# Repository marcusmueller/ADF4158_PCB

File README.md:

# ADF4158 + HMC391 PCB

This project is a PCB that contains an
[ADF4158](https://www.analog.com/en/products/adf4158.html) direct
modulation/waveform generating fractional-N frequency synthesizer and a
[HMC391](https://www.analog.com/en/products/hmc391.html) 3.9 - 4.45 GHz VCO. The
board is primarily intended as an LO source for a 10 GHz FMCW radar inspired by
the
[ADALM-PHASER](https://wiki.analog.com/resources/eval/user-guides/circuits-from-the-lab/cn0566/overview_setup). The
VCO output can be used with a subharmonic mixer and an IF around 1.6 GHz to
cover the 10 - 10.5 GHz amateur radio band.

The board runs from a 12 - 16 VDC supply, exposes all the control pins of the
ADF4158 in a 2.58 mm pin header (3.3V logic) and includes an optional 10 MHz
reference input. The BOM cost is around 45€.

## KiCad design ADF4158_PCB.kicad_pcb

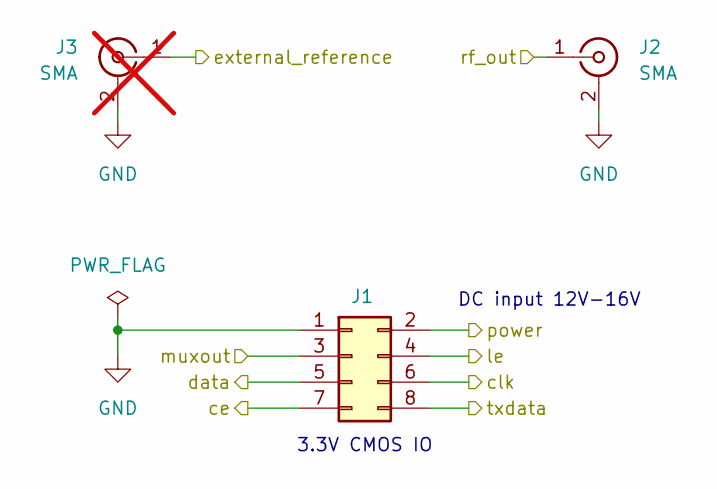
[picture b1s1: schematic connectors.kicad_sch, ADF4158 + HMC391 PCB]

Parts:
J1: Conn_02x04_Odd_Even; PinHeader_2x04_P2.54mm_Vertical; Digikey Part Number 2057-PH2-08-UA-ND
J2: SMA; WRL-23187; Digikey Part Number 1568-WRL-23187-ND
J3: SMA; WRL-23187; Digikey Part Number 1568-WRL-23187-ND; not fitted

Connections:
/ADF4158 + HMC391/ce: J1.7; also elsewhere on the board
/ADF4158 + HMC391/clk: J1.6; also elsewhere on the board
/ADF4158 + HMC391/data: J1.5; also elsewhere on the board
/ADF4158 + HMC391/external_reference: J3.1 (In); also elsewhere on the board
/ADF4158 + HMC391/le: J1.4; also elsewhere on the board
/ADF4158 + HMC391/txdata: J1.8; also elsewhere on the board
/Connectors/power: J1.2; also elsewhere on the board
/muxout: J1.3; also elsewhere on the board
/rf_out: J2.1 (In); also elsewhere on the board
GND: J1.1, J2.2 (Ext), J3.2 (Ext); also elsewhere on the board

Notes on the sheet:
DC input 12V-16V
3.3V CMOS IO

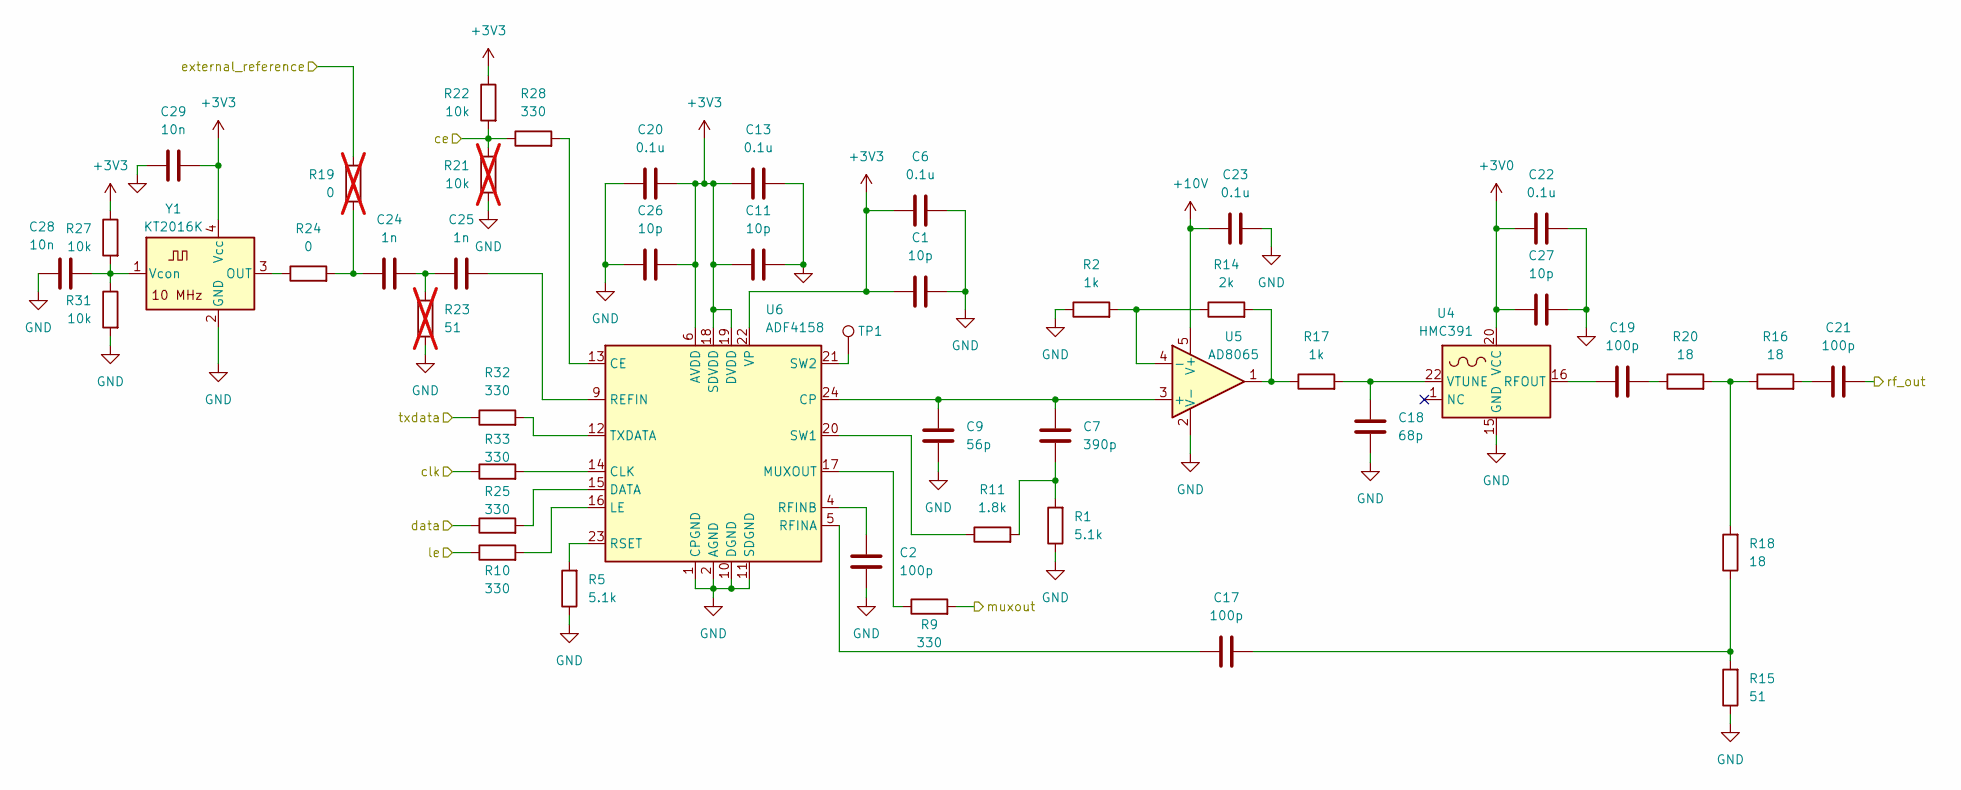
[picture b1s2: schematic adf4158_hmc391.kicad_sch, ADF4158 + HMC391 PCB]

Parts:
C1, C11, C26, C27: 10p; C_0402_1005Metric; Digikey Part Number 1276-1139-1-ND
C2, C17, C19, C21: 100p; C_0402_1005Metric; Digikey Part Number 1276-1025-1-ND
C6, C13, C20, C22, C23: 0.1u; C_0402_1005Metric; Digikey Part Number 1276-1002-1-ND
C7: 390p; C_0402_1005Metric; Digikey Part Number 490-1296-1-ND
C9: 56p; C_0402_1005Metric; Digikey Part Number 490-1288-1-ND
C18: 68p; C_0402_1005Metric; Digikey Part Number 490-5876-1-ND
C24, C25: 1n; C_0402_1005Metric; Digikey Part Number 1276-1032-1-ND
C28, C29: 10n; C_0402_1005Metric; Digikey Part Number 1276-1028-1-ND
R1, R5: 5.1k; R_0402_1005Metric; Digikey Part Number P5.1KDCCT-ND
R2, R17: 1k; R_0402_1005Metric; Digikey Part Number P1.00KLCT-ND
R9, R10, R25, R28, R32, R33: 330; R_0402_1005Metric; Digikey Part Number P330LCT-ND
R11: 1.8k; R_0402_1005Metric; Digikey Part Number P1.80KLCT-ND
R14: 2k; R_0402_1005Metric; Digikey Part Number P2.00KLCT-ND
R15: 51; R_0402_1005Metric; Digikey Part Number P51.0LCT-ND
R16, R18, R20: 18; R_0402_1005Metric; Digikey Part Number P18.0LCT-ND
R19: 0; R_0402_1005Metric; Digikey Part Number P0.0JCT-ND; not fitted
R21: 10k; R_0402_1005Metric; Digikey Part Number P10.0KLCT-ND; not fitted
R22, R27, R31: 10k; R_0402_1005Metric; Digikey Part Number P10.0KLCT-ND
R23: 51; R_0402_1005Metric; Digikey Part Number P51.0LCT-ND; not fitted
R24: 0; R_0402_1005Metric; Digikey Part Number P0.0JCT-ND
TP1: TestPoint; TestPoint_Pad_D2.0mm
U4: HMC391; QFN-24-1EP_4x4mm_P0.5mm_EP2.8x2.8mm; Digikey Part Number 505-HMC391LP4ECT-ND
U5: AD8065; TSOT-23-5; Digikey Part Number AD8065ARTZ-REELCT-ND
U6: ADF4158; LFCSP-24-1EP_4x4mm_P0.5mm_EP2.5x2.5mm; Digikey Part Number 505-ADF4158CCPZ-ND
Y1: KT2016K; Digikey Part Number 478-KT2016K10000ZAW33ZGKCT-ND

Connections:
+3V0: C22.2, C27.2, U4.20 (VCC); also elsewhere on the board
+3V3: C1.2, C6.2, C11.2, C13.2, C20.2, C26.2, C29.1, R22.1, R27.1, U6.6 (AVDD), U6.7 (AVDD), U6.8 (AVDD), U6.18 (SDVDD), U6.19 (DVDD), U6.22 (VP), Y1.4 (Vcc); also elsewhere on the board
+10V: C23.2, U5.5 (V+); also elsewhere on the board
/ADF4158 + HMC391/ce: R21.1, R22.2, R28.1; also elsewhere on the board
/ADF4158 + HMC391/clk: R33.1; also elsewhere on the board
/ADF4158 + HMC391/data: R25.1; also elsewhere on the board
/ADF4158 + HMC391/external_reference: R19.2; also elsewhere on the board
/ADF4158 + HMC391/le: R10.1; also elsewhere on the board
/ADF4158 + HMC391/txdata: R32.1; also elsewhere on the board
/muxout: R9.2; also elsewhere on the board
/rf_out: C21.2; also elsewhere on the board
GND: C1.1, C2.2, C6.1, C9.2, C11.1, C13.1, C18.2, C20.1, C22.1, C23.1, C26.1, C27.1, C28.1, C29.2, R1.1, R2.1, R5.1, R15.1, R21.2, R23.1, R31.2, U4.15 (GND), U4.25 (GND), U5.2 (V-), U6.1 (CPGND), U6.2 (AGND), U6.3 (AGND), U6.10 (DGND), U6.11 (SDGND), U6.25 (AGND), Y1.2 (GND); also elsewhere on the board
unnamed: C7.2, R1.2, R11.2
unnamed: C17.2, R15.2, R18.1
unnamed: C19.2, R20.1
unnamed: C21.1, R16.2
unnamed: C24.1, R19.1, R24.2
unnamed: C24.2, C25.1, R23.2
unnamed: R14.2, R17.1, U5.1
unnamed: R16.1, R18.2, R20.2
unnamed: C19.1, U4.16 (RFOUT)
unnamed: C18.1, R17.2, U4.22 (VTUNE)
unnamed: C7.1, C9.1, U5.3 (+), U6.24 (CP)
unnamed: R2.2, R14.1, U5.4 (-)
unnamed: R28.2, U6.13 (CE)
unnamed: R33.2, U6.14 (CLK)
unnamed: R25.2, U6.15 (DATA)
unnamed: R10.2, U6.16 (LE)
unnamed: R9.1, U6.17 (MUXOUT)
unnamed: C25.2, U6.9 (REFIN)
unnamed: C17.1, U6.5 (RFINA)
unnamed: C2.1, U6.4 (RFINB)
unnamed: R5.2, U6.23 (RSET)
unnamed: R11.1, U6.20 (SW1)
unnamed: TP1.1, U6.21 (SW2)
unnamed: R32.2, U6.12 (TXDATA)
unnamed: R24.1, Y1.3 (OUT)
unnamed: C28.2, R27.2, R31.1, Y1.1 (Vcon)

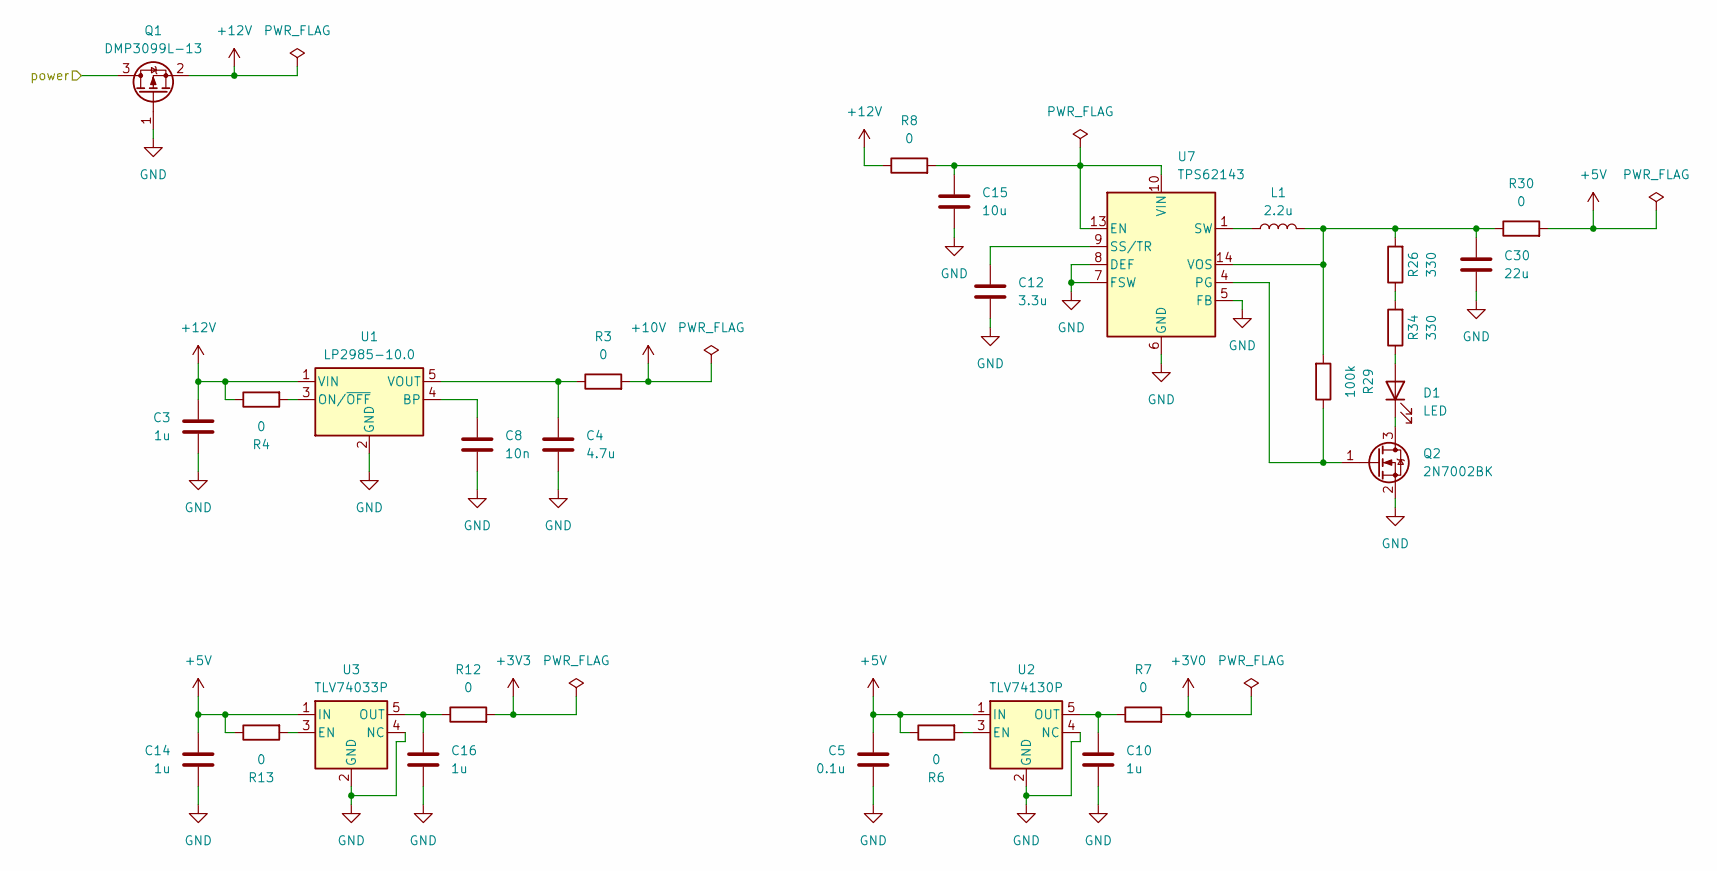
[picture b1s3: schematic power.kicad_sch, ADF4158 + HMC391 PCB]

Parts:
C3, C10, C14, C16: 1u; C_0603_1608Metric; Digikey Part Number 1276-1184-1-ND
C4: 4.7u; C_0805_2012Metric; Digikey Part Number 490-GRM21BR71C475ME51KCT-ND
C5: 0.1u; C_0402_1005Metric; Digikey Part Number 1276-1002-1-ND
C8: 10n; C_0402_1005Metric; Digikey Part Number 1276-1028-1-ND
C12: 3.3u; C_1206_3216Metric; Digikey Part Number 1276-1841-1-ND
C15: 10u; C_0805_2012Metric; Digikey Part Number 1276-2872-1-ND
C30: 22u; C_0603_1608Metric; Digikey Part Number 1276-1274-1-ND
D1: LED; LED_0603_1608Metric; Digikey Part Number 3147-B1931NG--20D001114U1930CT-ND
L1: 2.2u; L_1008_2520Metric; Digikey Part Number 490-10649-1-ND
Q1: DMP3099L-13; SOT-23-3; Digikey Part Number DMP3099L-13DICT-ND
Q2: 2N7002BK; SOT-23; Digikey Part Number 1727-4789-1-ND
R3, R4, R6, R7, R8, R12, R13, R30: 0; R_0402_1005Metric; Digikey Part Number P0.0JCT-ND
R26, R34: 330; R_0402_1005Metric; Digikey Part Number P330LCT-ND
R29: 100k; R_0402_1005Metric; Digikey Part Number P100KLCT-ND
U1: LP2985-10.0; SOT-23-5; Digikey Part Number 296-24263-1-ND
U2: TLV74130P; SOT-23-5; Digikey Part Number 296-50000-1-ND
U3: TLV74033P; SOT-23-5; Digikey Part Number 296-TLV74033PDBVRCT-ND
U7: TPS62143; VQFN-16-1EP_3x3mm_P0.5mm_EP1.68x1.68mm_ThermalVias; Digikey Part Number 296-39448-1-ND

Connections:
+3V0: R7.2; also elsewhere on the board
+3V3: R12.2; also elsewhere on the board
+5V: C5.1, C14.1, R6.1, R13.1, R30.2, U2.1 (IN), U3.1 (IN)
+10V: R3.2; also elsewhere on the board
+12V: C3.1, Q1.2 (S), R4.1, R8.1, U1.1 (VIN)
/Connectors/power: Q1.3 (D); also elsewhere on the board
GND: C3.2, C4.2, C5.2, C8.2, C10.2, C12.2, C14.2, C15.2, C16.2, C30.2, Q1.1 (G), Q2.2 (S), U1.2 (GND), U2.2 (GND), U2.4 (NC), U3.2 (GND), U3.4 (NC), U7.5 (FB), U7.6 (GND), U7.7 (FSW), U7.8 (DEF), U7.15 (GND), U7.16 (GND), U7.17 (GND); also elsewhere on the board
unnamed: D1.2 (A), R34.1
unnamed: D1.1 (K), Q2.3 (D)
unnamed: L1.1, U7.1 (SW), U7.2 (SW), U7.3 (SW)
unnamed: Q2.1 (G), R29.1, U7.4 (PG)
unnamed: R26.1, R34.2
unnamed: C8.1, U1.4 (BP)
unnamed: R4.2, U1.3 (ON/~OFF)
unnamed: C4.1, R3.1, U1.5 (VOUT)
unnamed: R6.2, U2.3 (EN)
unnamed: C10.1, R7.1, U2.5 (OUT)
unnamed: R13.2, U3.3 (EN)
unnamed: C16.1, R12.1, U3.5 (OUT)
unnamed: C15.1, R8.2, U7.10 (VIN), U7.11 (VIN), U7.12 (VIN), U7.13 (EN)
unnamed: C12.1, U7.9 (SS/TR)
unnamed: C30.1, L1.2, R26.2, R29.2, R30.1, U7.14 (VOS)

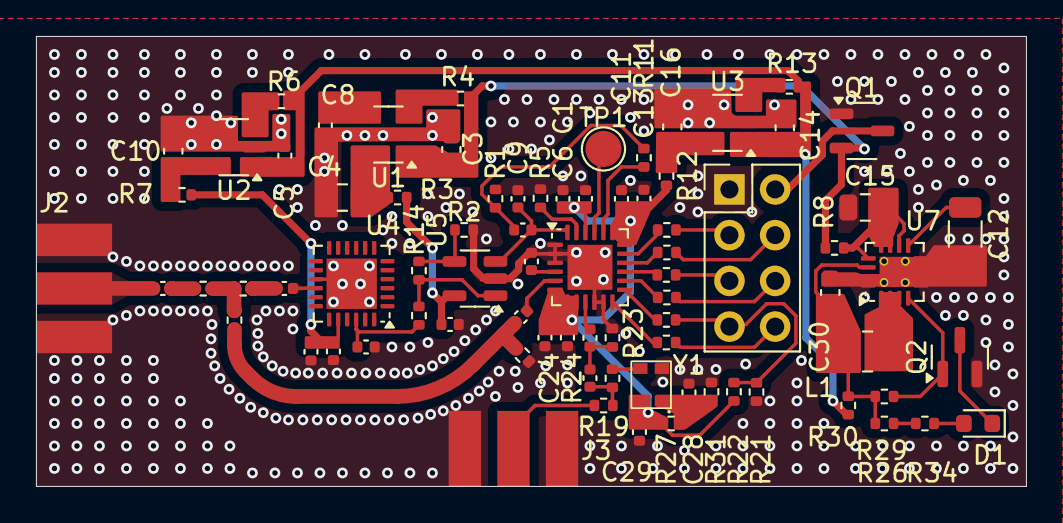
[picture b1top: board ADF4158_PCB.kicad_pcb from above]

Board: 2 copper layers, 55.0 x 25.0 mm, 80 parts (0 on the bottom side), 56 nets.

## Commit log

2025-04-12 add kicad project files
2025-04-12 add CI workflow
2025-04-12 update README
    Add links to Github pages and fabrication information.
2025-04-12 increase PCB render zoom
    Increase PCB render zoom to remove larger margin in the PNG file.
2025-04-12 add link to DigiKey list
2025-04-12 add PLL loop filter design file
2025-04-12 gerbers
